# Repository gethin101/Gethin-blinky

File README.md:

# Gethin Blinky
I made this project with Hackclub Blueprint's YSWS where I designed and built the PCB in KiCad, got it manufactured by JLCPCB and hand soldered on all the components at home.

The project schematic, PCB positioning, 3D model preview and JLCPCB cart screenshot are below:

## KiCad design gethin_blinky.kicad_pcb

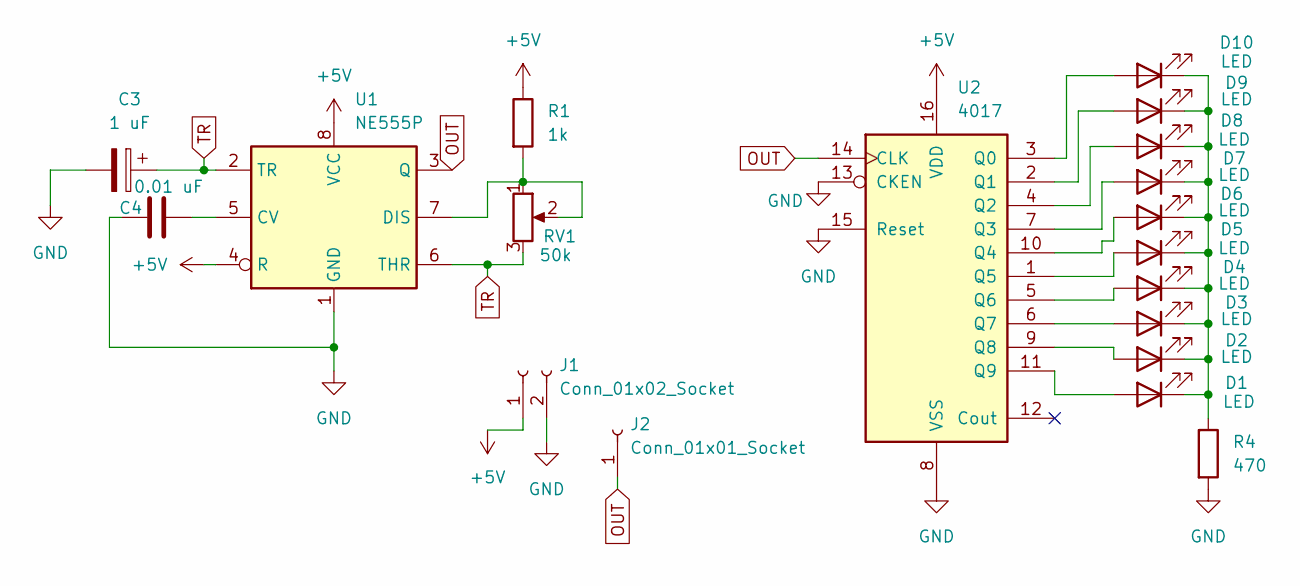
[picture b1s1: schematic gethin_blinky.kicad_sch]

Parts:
C3: 1 uF; CP_Radial_D5.0mm_P2.00mm
C4: 0.01 uF; C_Disc_D7.5mm_W2.5mm_P5.00mm
D1, D2, D3, D4, D5, D6, D7, D8, D9, D10: LED; LED_D3.0mm
J1: Conn_01x02_Socket; PinHeader_1x02_P2.54mm_Vertical
J2: Conn_01x01_Socket; PinHeader_1x01_P2.54mm_Vertical
R1: 1k; R_Axial_DIN0207_L6.3mm_D2.5mm_P7.62mm_Horizontal
R4: 470; R_Axial_DIN0207_L6.3mm_D2.5mm_P7.62mm_Horizontal
RV1: 50k; Potentiometer_Vishay_T93YA_Vertical
U1: NE555P; DIP-8_W7.62mm
U2: 4017; N16

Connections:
+5V: J1.1, R1.1, U1.4 (R), U1.8 (VCC), U2.16 (VDD)
GND: C3.2, C4.2, J1.2, R4.2, U1.1 (GND), U2.8 (VSS), U2.13 (CKEN), U2.15 (Reset)
unnamed: D1.2 (A), U2.11 (Q9)
unnamed: D1.1 (K), D2.1 (K), D3.1 (K), D4.1 (K), D5.1 (K), D6.1 (K), D7.1 (K), D8.1 (K), D9.1 (K), D10.1 (K), R4.1
unnamed: D2.2 (A), U2.9 (Q8)
unnamed: D3.2 (A), U2.6 (Q7)
unnamed: D4.2 (A), U2.5 (Q6)
unnamed: D5.2 (A), U2.1 (Q5)
unnamed: D6.2 (A), U2.10 (Q4)
unnamed: D7.2 (A), U2.7 (Q3)
unnamed: D8.2 (A), U2.4 (Q2)
unnamed: D9.2 (A), U2.2 (Q1)
unnamed: D10.2 (A), U2.3 (Q0)
unnamed: C4.1, U1.5 (CV)
unnamed: R1.2, RV1.1, RV1.2, U1.7 (DIS)
OUT: J2.1, U1.3 (Q), U2.14 (CLK)
TR: C3.1, RV1.3, U1.2 (TR), U1.6 (THR)

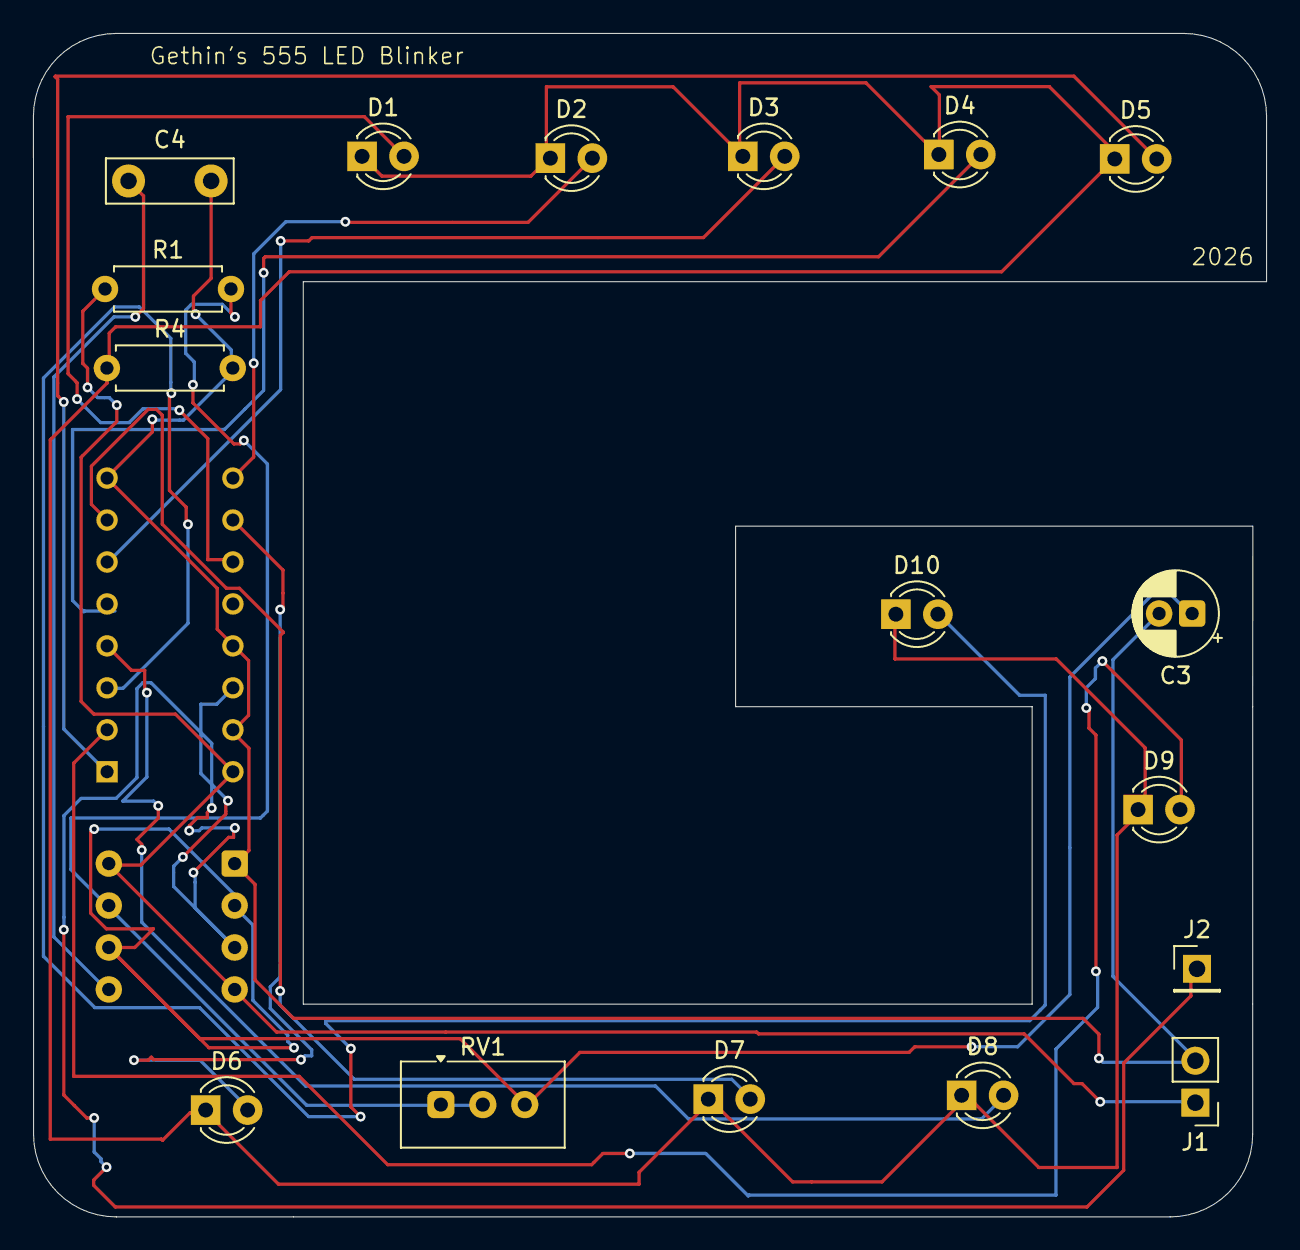
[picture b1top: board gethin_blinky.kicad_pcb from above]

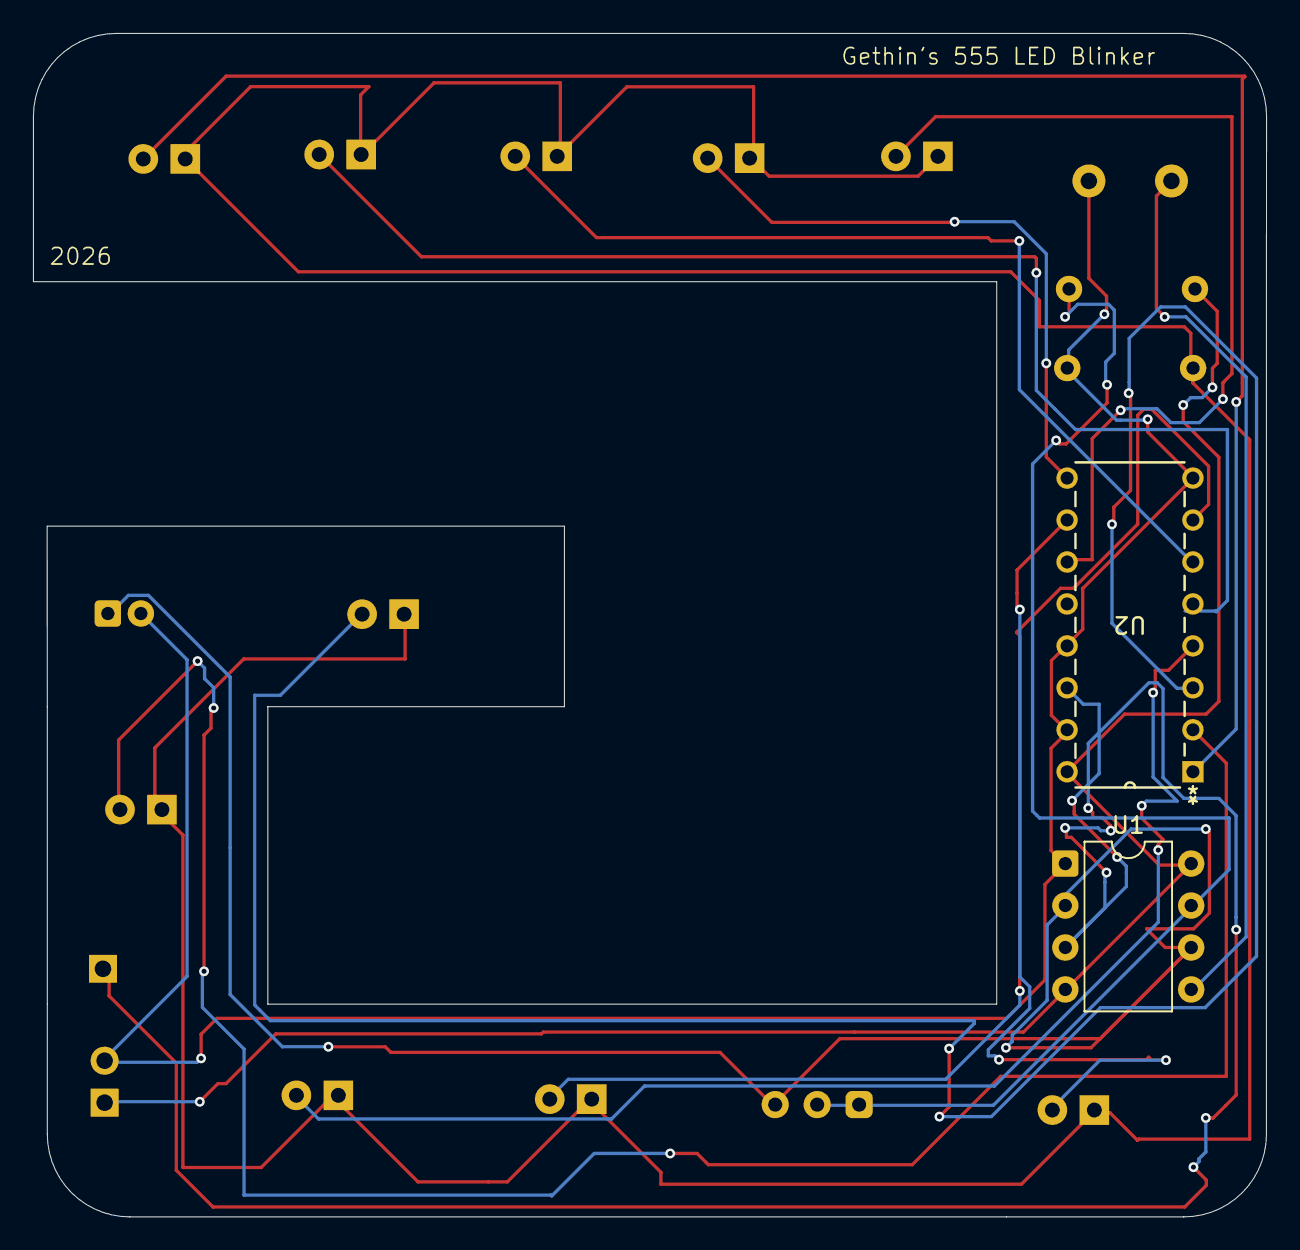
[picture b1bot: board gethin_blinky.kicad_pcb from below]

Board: 2 copper layers, 74.7 x 71.7 mm, 19 parts (2 on the bottom side), 17 nets.

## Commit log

2026-02-22 Create 1
2026-02-22 Rename Screenshot 2026-02-22 083259.png to 3D.png
2026-02-22 Rename Screenshot 2026-02-22 083305.png to PCB.png
2026-02-22 Rename Screenshot 2026-02-22 083313.png to SCHEM.png
2026-02-22 Rename Screenshot 2026-02-22 084302.png to JLCPCB_cart.png
